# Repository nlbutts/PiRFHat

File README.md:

# PiRFHat
This project is a Pi Hat that incorporates an ST Teseo GPS receiver and a RFM9x LoRa module.

# GPS
The GPS receiver uses gpsd and is pretty straigtforward to get setup
```
apt-get install gpsd
```

Next modify **/lib/systemd/system/gpsd.service** and change the following file:
```
ExecStart=/usr/sbin/gpsd $GPSD_OPTIONS /dev/ttyS0
```

TBD working on Python code to send and receive data

# LoRa

The rf_testing.py file is a simple command line system to run BER and PER tests between two devices. It also supports simple file transfer.

## BER

To perform BER testing on the receiver do the following:
```
python rf_testing.py -n 100 -r --pirfhat
```

On the transmit do the following:
```
python rf_testing.py --pirfhat --delay=0.01
```

This will transmit 100 messages then the receiver will exit and print the BER and PER.

## File Transfer
```
python rf_testing.py --pirfhat --receivefile foo.bar
```

```
python rf_testing.py --pirfhat --sendfile foo.bar
```

# File Transfer Protocol
The file transfer protocol is very simple. You can use the LoRa header to address a particular node. The file transfer payload is defined below:

| Command | Sequence number | Payload |
| ------- | ----------------| --------- |
| Start Command (0) | Sequence Number | Bytes to transfer | 32-bit CRC | Data |
| Continuous Trasnfer (1) | Sequence Number | Data |

The **Sequence Number** is a monotonically increasing 32-bit number that indicates which packet this is.

## Start File Transfer
The **Start File Transfer** command

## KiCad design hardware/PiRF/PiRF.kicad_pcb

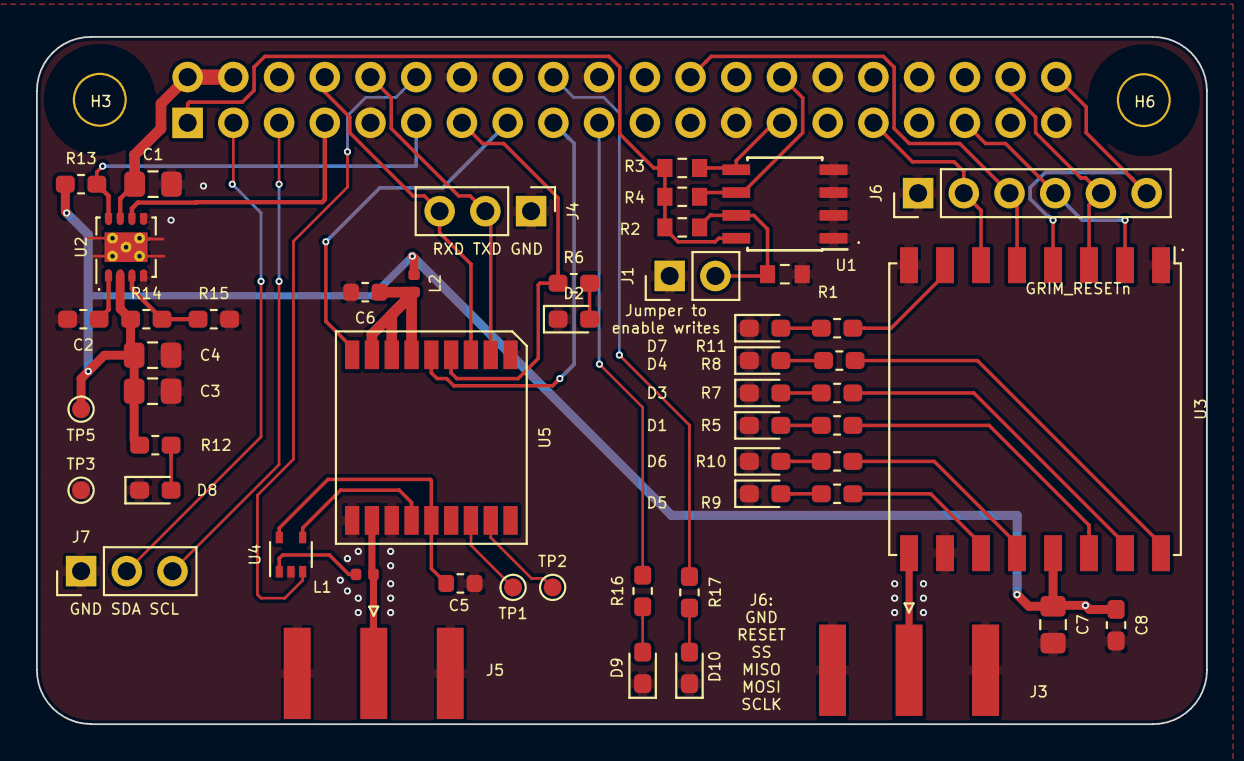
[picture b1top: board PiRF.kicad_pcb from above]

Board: 2 copper layers, 65.0 x 38.2 mm, 55 parts (1 on the bottom side), 50 nets.

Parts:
C1, C3, C4, C7: 10u; C_0805_2012Metric_Pad1.15x1.40mm_HandSolder
C2, C8: 0.1u; C_0603_1608Metric_Pad1.05x0.95mm_HandSolder
C5, C6: 56P; C_0603_1608Metric
D1, D2, D3, D4, D5, D6, D7, D8, D9, D10: LED; LED_0603_1608Metric_Pad1.05x0.95mm_HandSolder
H3, H6: 3mm_Mounting_Hole; NPTH_3mm_ID
J1: CONN_01X02; PinHeader_1x02_P2.54mm_Vertical
J2: 40HAT; PinSocket_2x20_P2.54mm_Vertical
J3, J5: Conn_Coaxial; SMA_Amphenol_132289_EdgeMount
J4, J7: Conn_01x03; PinHeader_1x03_P2.54mm_Vertical
J6: Conn_01x06; PinHeader_1x06_P2.54mm_Vertical
L1, L2: 27n; L_0402_1005Metric
R1: DNP; R_0603_1608Metric_Pad0.84x1.00mm_HandSolder
R2: 10K; R_0603_1608Metric_Pad0.84x1.00mm_HandSolder
R3, R4: 3.9K; R_0603_1608Metric_Pad0.84x1.00mm_HandSolder
R5, R6, R7, R8, R9, R10, R11, R12, R16, R17: 330; R_0603_1608Metric_Pad1.05x0.95mm_HandSolder
R13: 10K; R_0603_1608Metric_Pad1.05x0.95mm_HandSolder
R14: 15.8k; R_0603_1608Metric_Pad1.05x0.95mm_HandSolder
R15: 9.53k; R_0603_1608Metric_Pad1.05x0.95mm_HandSolder
TP1, TP2, TP3, TP5: TestPoint; TestPoint_Pad_D1.0mm
U1: CAT24C32; SOIC-8_3.9x4.9mm_P1.27mm
U2: TPS7A19; Texas_S-PVSON-N8_ThermalVias
U3: RFM95W-915S2; HOPERF_RFM9XW_SMD
U4: TPS2294x; SOT-353_SC-70-5
U5: ST_Teseo; TESEO-LIV3R

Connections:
+3V3: C3.1, C4.1, C7.1, C8.1, L2.1, R12.1, R13.1, R14.1, TP5.1, U2.2, U3.13
/ANT_OFF: U4.4, U5.13
/GPS_ANT_OC: J2.12, U4.3
/GPS_PPS: J2.13, R6.1, U5.4
/GPS_RESETn: J2.15, U5.9
/GPS_WAKE: J2.17, U5.5
/HAT_3V3: J2.1, R2.1, R3.1, R4.1, U1.8
/HAT_PG: J2.11, R13.2, U2.8
/HAT_PWR_EN: J2.7, U2.6
/I2C_SCL: J2.5, J7.3
/I2C_SDA: J2.3, J7.2
/ID_SC_EEPROM: J2.28, R4.2, U1.6
/ID_SD_EEPROM: J2.27, R3.2, U1.5
/MISO: J2.35, J6.4, U3.2
/MOSI: J2.38, J6.5, U3.3
/P5V_HAT: C1.1, J2.2, J2.4, U2.7
/PI_LED_1: J2.19, R16.1
/PI_LED_2: J2.18, R17.1
/RFM_RESET: J2.31, J6.2, U3.6
/SCLK: J2.40, J6.6, U3.4
/SS: J2.24, J6.3, U3.5
/UART_RXD: J2.8, J4.3, U5.3
/UART_TXD: J2.10, J4.2, U5.2
/VCC_RF: C5.1, U4.5, U5.14
GND: C1.2, C2.2, C3.2, C4.2, C5.2, C6.2, C7.2, C8.2, D1.1, D2.1, D3.1, D4.1, D5.1, D6.1, D7.1, D8.1, D9.1, D10.1, J1.1, J2.6, J2.9, J2.14, J2.20, J2.25, J2.30, J2.34, J2.39, J3.2, J4.1, J5.2, J6.1, J7.1, R1.2, R15.2, TP3.1, U1.1, U1.2, U1.3, U1.4, U2.4, U2.5, U2.9, U3.1, U3.8, U3.10, U4.2, U5.1, U5.10, U5.12
unnamed: C2.1, U2.1
unnamed: C6.1, L2.2, U5.6, U5.7, U5.8
unnamed: D1.2, R5.2
unnamed: D2.2, R6.2
unnamed: D3.2, R7.2
unnamed: D4.2, R8.2
unnamed: D5.2, R9.2
unnamed: D6.2, R10.2
unnamed: D7.2, R11.2
unnamed: D8.2, R12.2
unnamed: D9.2, R16.2
unnamed: D10.2, R17.2
unnamed: J1.2, R1.1, R2.2, U1.7
unnamed: J3.1, U3.9
unnamed: J5.1, L1.2, U5.11
unnamed: L1.1, U4.1
unnamed: R5.1, U3.14
unnamed: R7.1, U3.15
unnamed: R8.1, U3.16
unnamed: R9.1, U3.11
unnamed: R10.1, U3.12
unnamed: R11.1, U3.7
unnamed: R14.2, R15.1, U2.3
unnamed: TP1.1, U5.16
unnamed: TP2.1, U5.17

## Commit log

2019-09-16 Initial add
2019-09-19 Updated the design. Ready to start layout.
2019-09-19 Updated and started to route signals.
2019-09-20 Finished layout
2019-10-06 Added GPS to the design, haven't routed the design yet.
2019-10-06 Removed the DWM1000 and replaced it with GPS.
2019-10-06 Added an info section to the silkscreen.
2019-10-06 Added a cutout for the camera.
2019-10-25 Update part numbers.
2019-11-25 Order Rev B
2020-01-27 Added some rough test software.
2020-02-13 Updated the rf_testing.py file to support both the Adafruit RFM9x boards and this project PiRFHat.
2020-02-16 Updated the code to transfer files.
2020-02-17 Added a camera transfer program.
2020-02-24 Added a receiver app that uses Flask to display images in browser.
2020-02-26 Did some updates.
2020-02-27 Updated to display RSSI, SNR, and time of last image.
2020-02-28 Tweaked some settings. Added the ability to specify image resolution.
2020-03-20 Started to try and add FSK support.
2020-05-02 I have FSK transfers working.
2020-05-03 Have high speed 256 byte packets working.

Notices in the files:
hardware/PiRF/PiRF.kicad_pcb:
Copyright 2019
